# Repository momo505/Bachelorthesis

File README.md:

# Bachelorthesis
Repo für Bachelorarbeit

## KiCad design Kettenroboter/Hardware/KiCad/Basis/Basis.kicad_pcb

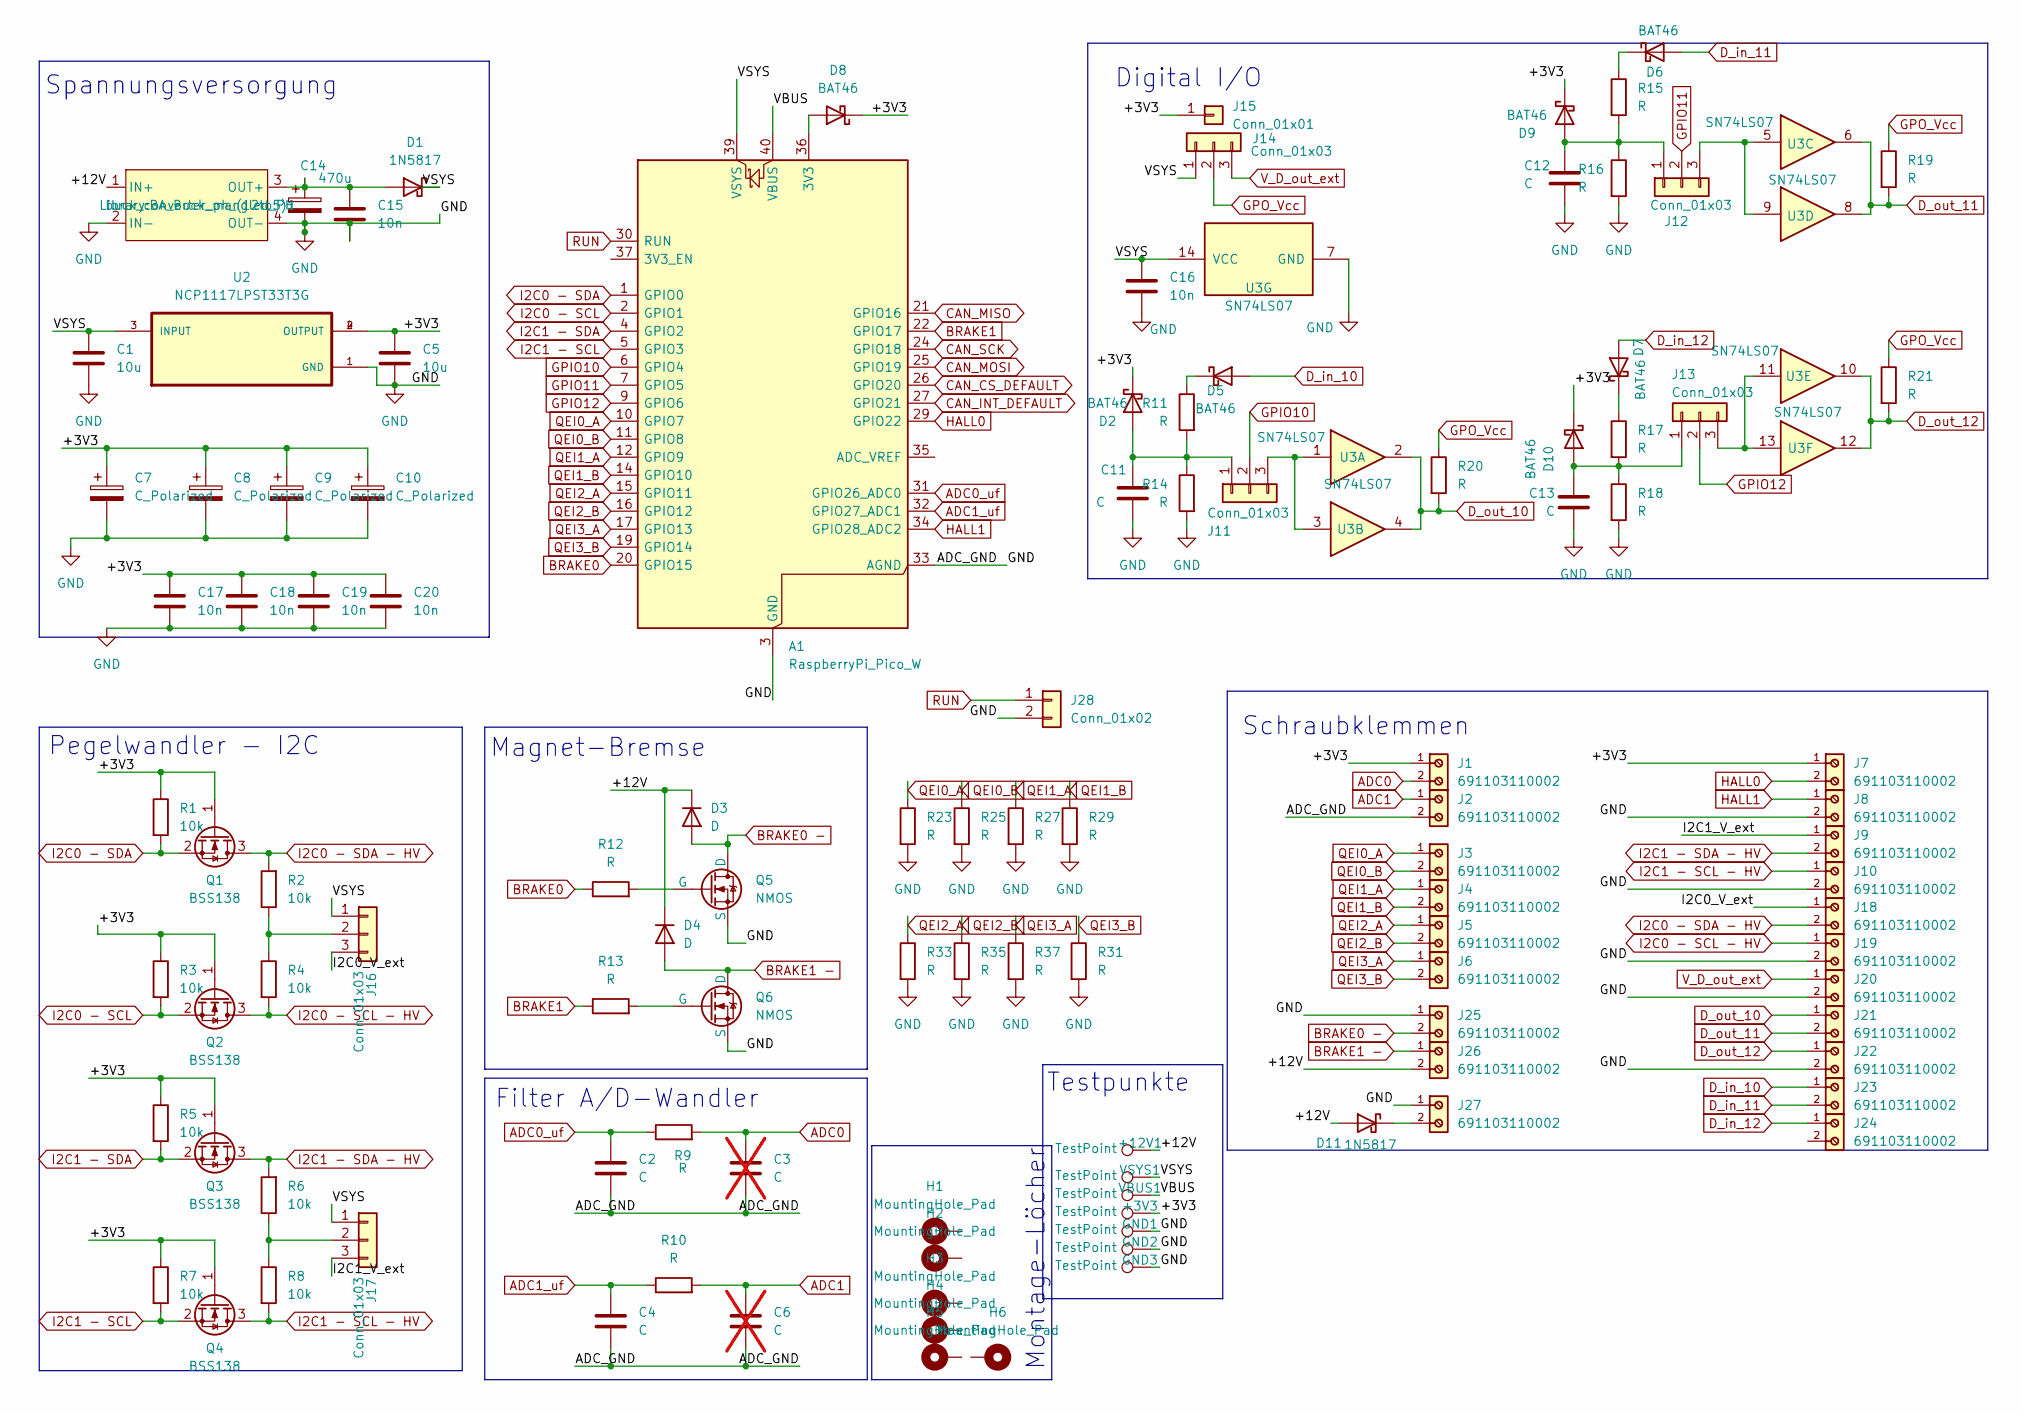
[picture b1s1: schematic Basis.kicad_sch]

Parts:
+3V3, +12V1: TestPoint; TestPoint_Pad_D2.5mm
A1: RaspberryPi_Pico_W; RaspberryPi_Pico_Common_THT
C1, C5: 10u; C_1206_3216Metric_Pad1.33x1.80mm_HandSolder
C2, C4, C11, C12, C13: C; C_1206_3216Metric_Pad1.33x1.80mm_HandSolder
C3, C6: C; C_1206_3216Metric_Pad1.33x1.80mm_HandSolder; not fitted
C7, C8, C9, C10: C_Polarized; CP_Radial_D5.0mm_P2.50mm
C14: 470u; CP_Radial_D5.0mm_P2.50mm
C15, C16, C17, C18, C19, C20: 10n; C_1206_3216Metric_Pad1.33x1.80mm_HandSolder
D1, D11: 1N5817; D_DO-41_SOD81_P10.16mm_Horizontal
D2, D5, D6, D7, D8, D9, D10: BAT46; D_DO-35_SOD27_P7.62mm_Horizontal
D3, D4: D; D_5KPW_P7.62mm_Vertical_AnodeUp
GND1, GND2, GND3: TestPoint; TestPoint_Pad_D2.5mm
H1, H2: MountingHole_Pad; MountingHole_3.2mm_M3_Pad_Via
H3, H4, H5, H6: MountingHole_Pad; MountingHole_4.3mm_M4_Pad_Via
J1, J2, J3, J4, J5, J6, J7, J8, J9, J10, J18, J19, J20, J21, J22, J23, J24, J25, J26, J27: 691103110002; WR-TBL_V3_2pin_691103110002
J11, J12, J13, J14, J16, J17: Conn_01x03; PinHeader_1x03_P2.54mm_Vertical
J15: Conn_01x01; PinHeader_1x01_P2.54mm_Vertical
J28: Conn_01x02; PinHeader_1x02_P2.54mm_Vertical
Q1, Q2, Q3, Q4: BSS138; SOT-23
Q5, Q6: NMOS; SOT-23_AO3400
R1, R2, R3, R4, R5, R6, R7, R8: 10k; R_1206_3216Metric_Pad1.30x1.75mm_HandSolder
R9, R10, R11, R12, R13, R14, R15, R16, R17, R18, R19, R20, R21, R23, R25, R27, R29, R31, R33, R35, R37: R; R_1206_3216Metric_Pad1.30x1.75mm_HandSolder
U2: NCP1117LPST33T3G; NCP1117_SOT230P700X175-4N
U3: SN74LS07; SOIC127P600X175-14N
VBUS1: TestPoint; TestPoint_Pad_D2.5mm
VSYS1: TestPoint; TestPoint_Pad_D2.5mm
buck_converter_ph_(12to5)1: BA_Buck_mangled_PH

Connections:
/+3V3: +3V3.1, C5.1, C7.1, C8.1, C9.1, C10.1, C17.1, C18.1, C19.1, C20.1, D2.1 (K), D8.1 (K), D9.1 (K), D10.1 (K), J1.1, J7.1, J15.1, Q1.1 (G), Q2.1 (G), Q3.1 (G), Q4.1 (G), R1.1, R3.1, R5.1, R7.1, U2.2 (OUTPUT), U2.4 (OUTPUT)
/+12V: +12V1.1, D3.1 (K), D4.1 (K), D11.2 (A), J26.2, buck_converter_ph_(12to5)1.1 (IN+)
/I2C0_V_ext: J16.3, J18.1
/I2C1_V_ext: J9.1, J17.3
/VBUS: A1.40 (VBUS), VBUS1.1
/VSYS: A1.39 (VSYS), C1.1, C16.1, D1.1 (K), J14.1, J16.1, J17.1, U2.3 (INPUT), U3.14 (VCC), VSYS1.1
ADC0: C3.1, J1.2, R9.2
ADC0_uf: A1.31 (GPIO26_ADC0), C2.1, R9.1
ADC1: C6.1, J2.1, R10.2
ADC1_uf: A1.32 (GPIO27_ADC1), C4.1, R10.1
BRAKE0: A1.20 (GPIO15), R12.1
BRAKE0 -: D3.2 (A), J25.2, Q5.1 (D)
BRAKE1: A1.22 (GPIO17), R13.1
BRAKE1 -: D4.2 (A), J26.1, Q6.1 (D)
CAN_CS_DEFAULT: A1.26 (GPIO20)
CAN_INT_DEFAULT: A1.27 (GPIO21)
CAN_MISO: A1.21 (GPIO16)
CAN_MOSI: A1.25 (GPIO19)
CAN_SCK: A1.24 (GPIO18)
D_in_10: D5.2 (A), J23.1
D_in_11: D6.2 (A), J23.2
D_in_12: D7.2 (A), J24.1
D_out_10: J21.1, R20.2, U3.2, U3.4
D_out_11: J21.2, R19.2, U3.6, U3.8
D_out_12: J22.1, R21.2, U3.10, U3.12
GND: A1.3 (GND), A1.8 (GND), A1.13 (GND), A1.18 (GND), A1.23 (GND), A1.28 (GND), A1.33 (AGND), A1.38 (GND), C1.2, C2.2, C3.2, C4.2, C5.2, C6.2, C7.2, C8.2, C9.2, C10.2, C11.2, C12.2, C13.2, C14.2, C15.2, C16.2, C17.2, C18.2, C19.2, C20.2, GND1.1, GND2.1, GND3.1, J2.2, J8.2, J10.2, J19.2, J20.2, J22.2, J25.1, J27.1, J28.2, Q5.3 (S), Q6.3 (S), R14.2, R16.2, R18.2, R23.2, R25.2, R27.2, R29.2, R31.2, R33.2, R35.2, R37.2, U2.1 (GND), U3.7 (GND), buck_converter_ph_(12to5)1.2 (IN-), buck_converter_ph_(12to5)1.4 (OUT-)
GPIO10: A1.6 (GPIO4), J11.2
GPIO11: A1.7 (GPIO5), J12.2
GPIO12: A1.9 (GPIO6), J13.2
GPO_Vcc: J14.2, R19.1, R20.1, R21.1
HALL0: A1.29 (GPIO22), J7.2
HALL1: A1.34 (GPIO28_ADC2), J8.1
I2C0 - SCL: A1.2 (GPIO1), Q2.2 (S), R3.2
I2C0 - SCL - HV: J19.1, Q2.3 (D), R4.2
I2C0 - SDA: A1.1 (GPIO0), Q1.2 (S), R1.2
I2C0 - SDA - HV: J18.2, Q1.3 (D), R2.2
I2C1 - SCL: A1.5 (GPIO3), Q4.2 (S), R7.2
I2C1 - SCL - HV: J10.1, Q4.3 (D), R8.2
I2C1 - SDA: A1.4 (GPIO2), Q3.2 (S), R5.2
I2C1 - SDA - HV: J9.2, Q3.3 (D), R6.2
unnamed: A1.36 (3V3), D8.2 (A)
unnamed: C14.1, C15.1, D1.2 (A), buck_converter_ph_(12to5)1.3 (OUT+)
unnamed: C11.1, D2.2 (A), J11.1, R11.2, R14.1
unnamed: D5.1 (K), R11.1
unnamed: D6.1 (K), R15.1
unnamed: D7.1 (K), R17.1
unnamed: C12.1, D9.2 (A), J12.1, R15.2, R16.1
unnamed: C13.1, D10.2 (A), J13.1, R17.2, R18.1
unnamed: D11.1 (K), J27.2
unnamed: J11.3, U3.1, U3.3
unnamed: J12.3, U3.5, U3.9
unnamed: J13.3, U3.11, U3.13
unnamed: J16.2, R2.1, R4.1
unnamed: J17.2, R6.1, R8.1
unnamed: Q5.2 (G), R12.2
unnamed: Q6.2 (G), R13.2
QEI0_A: A1.10 (GPIO7), J3.1, R23.1
QEI0_B: A1.11 (GPIO8), J3.2, R25.1
QEI1_A: A1.12 (GPIO9), J4.1, R27.1
QEI1_B: A1.14 (GPIO10), J4.2, R29.1
QEI2_A: A1.15 (GPIO11), J5.1, R33.1
QEI2_B: A1.16 (GPIO12), J5.2, R35.1
QEI3_A: A1.17 (GPIO13), J6.1, R37.1
QEI3_B: A1.19 (GPIO14), J6.2, R31.1
RUN: A1.30 (RUN), J28.1
V_D_out_ext: J14.3, J20.1

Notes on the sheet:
Spannungsversorgung
Magnet-Bremse
Pegelwandler - I2C
Testpunkte
Digital I/O
Schraubklemmen
Montage-Löcher
Filter A/D-Wandler

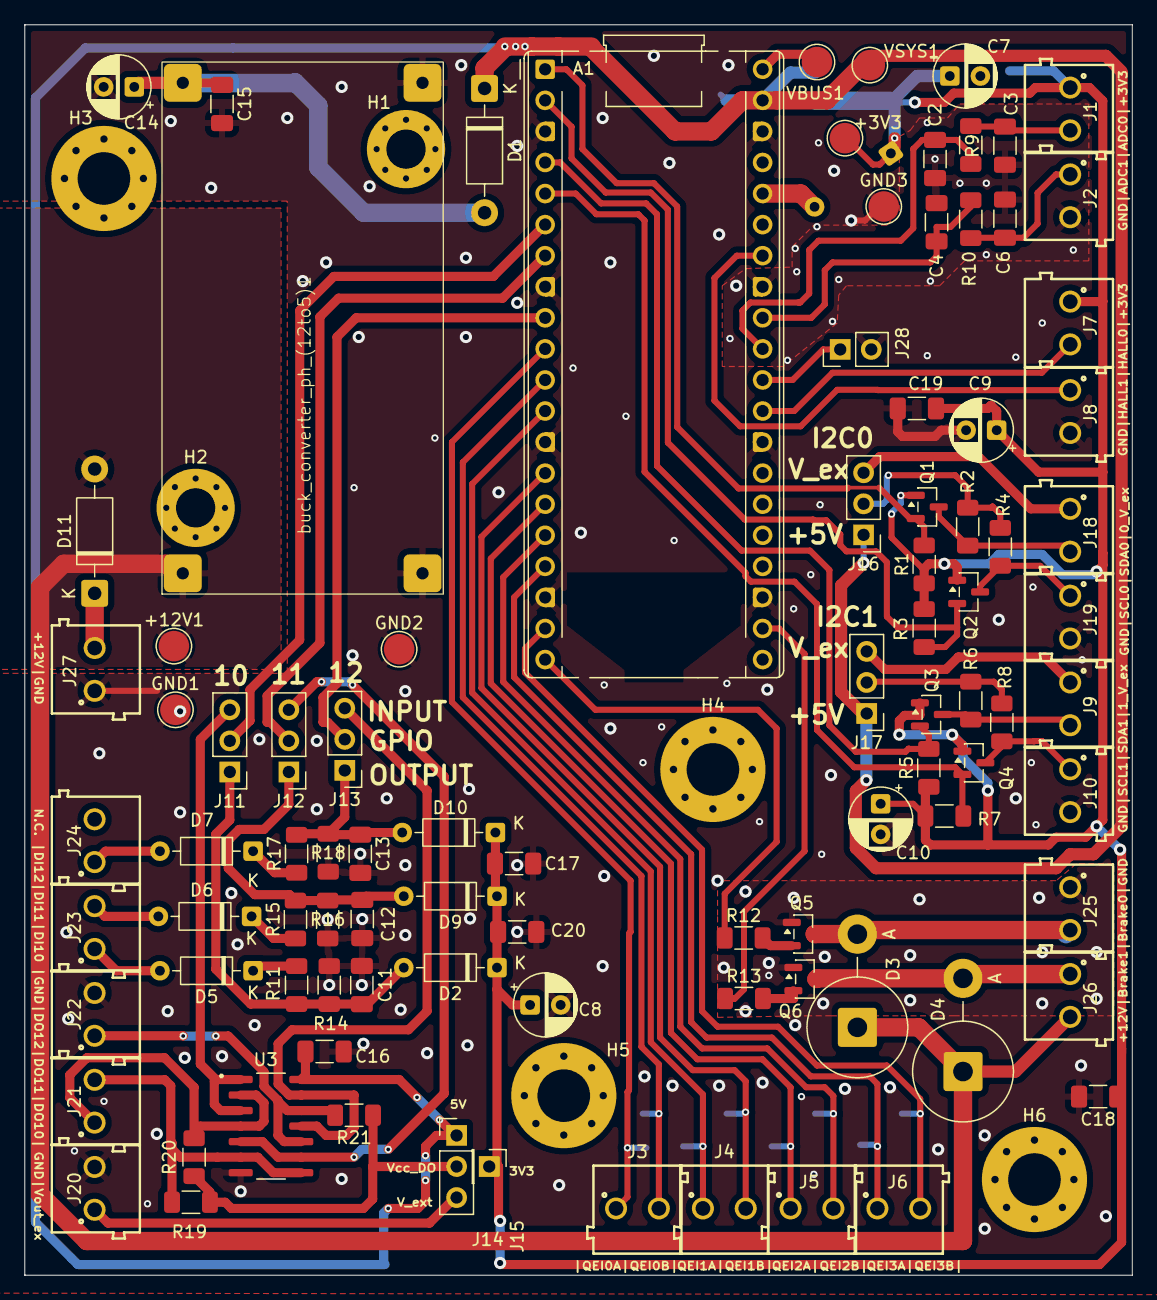
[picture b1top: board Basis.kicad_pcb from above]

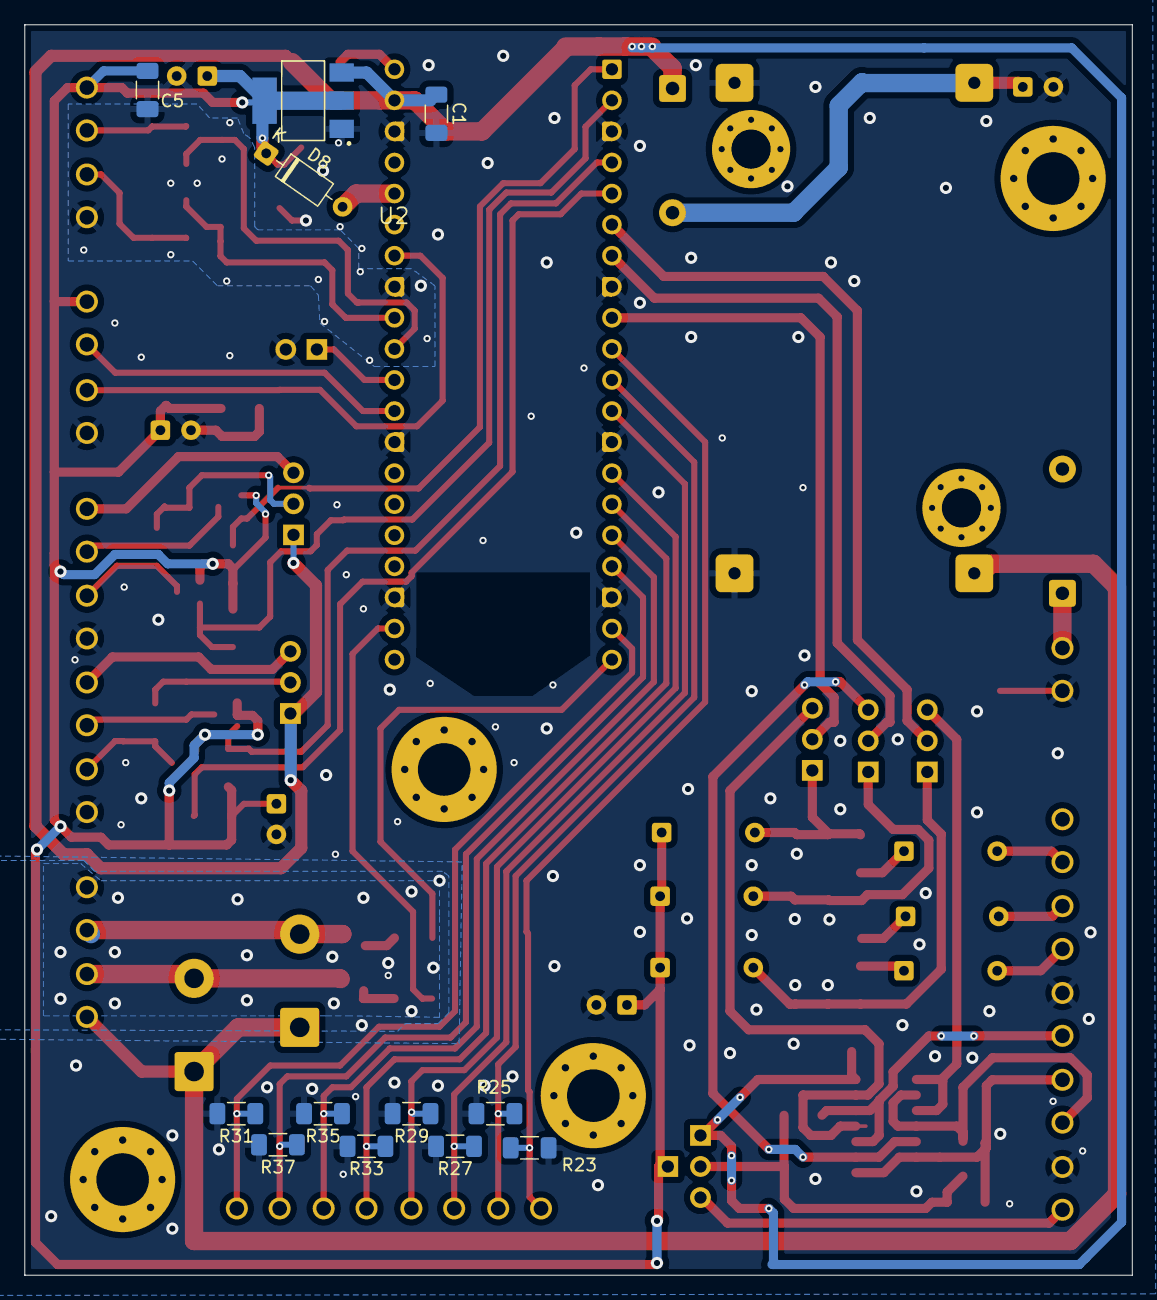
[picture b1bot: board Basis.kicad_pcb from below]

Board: 2 copper layers, 90.6 x 102.2 mm, 111 parts (12 on the bottom side), 61 nets.

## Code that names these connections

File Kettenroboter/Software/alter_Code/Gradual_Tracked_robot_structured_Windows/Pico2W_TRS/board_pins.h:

#ifndef pico2_trs_board_pinout
#define pico2_trs_board_pinout

#define I2C0_SDA 0
#define I2C0_SCL 1

#define I2C1_SDA 2
#define I2C1_SDA 3

#define DIO_1 4
#define DIO_2 5
#define DIO_3 5

#define QEI0_A 7
#define QEI0_B 8
#define QEI1_A 9
#define QEI1_B 10
#define QEI2_A 11
#define QEI2_B 12
#define QEI3_A 13
#define QEI3_B 14

#define BRAKE_A 15
#define BRAKE_B 17

#define HALL_A 29
#define HALL_B 28

#endif

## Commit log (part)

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2025-12-03 alles was bleibt vom alten Repo übernommen
2025-12-03 Add repository description to README
    Added a description for the Bachelor thesis repository.
2026-02-07 geändert: Pico2W_TRS/Pico2W_TRS.ino
2026-02-07 Zum Commit vorgemerkte Änderungen: neue Datei: KiCad/Basis/Basis-backups/Basis-2026-01-28_145330.zip neue Datei: KiCad/Basis/Basis-backups/Basis-2026-01-28_151514.zip neue Datei: KiCad/Basis/Basis-ba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
2026-02-12 Postbox Additions
    added code for postbox (in ino, has to move to cpp and h)
2026-02-17 neue Datei: Kettenroboter/Software/alter_Code/Gradual_Tracked_robot_structured_Windows/Pico2W_TRS/spi_helpers.cpp neue Datei: Kettenroboter/Software/alter_Code/Gradual_Tracked_robot_structured_Window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
2026-02-17 Auf Branch sw_job_division Zum Commit vorgemerkte Änderungen: geändert: Kettenroboter/Software/alter_Code/Gradual_Tracked_robot_structured_Windows/Pico2W_TRS/Pico2W_TRS.ino geändert: Kettenroboter/So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
2026-02-17 Auf Branch sw_pio_dev Zum Commit vorgemerkte Änderungen: geändert: qei.pio neue Datei: qei.pio.h
2026-02-19 Auf Branch sw_pio_dev Zum Commit vorgemerkte Änderungen: geändert: Kettenroboter/Software/alter_Code/Gradual_Tracked_robot_structured_Windows/Pico2W_TRS/Pico2W_TRS.ino geändert: Kettenroboter/Softwar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
2026-02-19 Ergänzungen Schaltung
2026-02-26 Nets korrigiert, etc
2026-02-26 Neues Pico W Symol & Footprint
2026-03-11 pcb layout fnished
2026-03-17 Fast finale Version
    Nach Crash gefixt
2026-03-19 final final final
2026-03-25 Auf Branch sw_pio_dev Zum Commit vorgemerkte Änderungen: umbenannt: pio_qei.cpp -> PIO/pio_qei.cpp umbenannt: pio_qei.h -> PIO/pio_qei.h umbenannt: qei.pio -> PIO/qei.pio umbenannt: qei.pio.h -> PIO/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
2026-04-02 neue Datei: Kettenroboter/Software/alter_Code/Gradual_Tracked_robot_structured_Windows/Pico2W_TRS/board_pins.h
2026-04-20 All Parts placed (BOM)
2026-04-20 Auf Branch sw_pio_dev Zum Commit vorgemerkte Änderungen: neue Datei: Kettenroboter/Software/Pico2W_TRS_Testup/LA-Bus-reads/MotorAB-I2C-reads/i2c.pvs neue Datei: Kettenroboter/Software/Pico2W_TRS_Test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
2026-04-29 Auf Branch sw_pio_dev Zum Commit vorgemerkte Änderungen: neue Datei: Kettenroboter/Software/Pico2W_TRS_Testup/PIO/pioasm.exe neue Datei: Kettenroboter/Software/Pico2W_TRS_Testup/PIO/qei.pio geändert: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
2026-05-26 On branch development Changes to be committed: new file: Kettenroboter/Software/Pico2W_TRS_Testup/PID.cpp new file: Kettenroboter/Software/Pico2W_TRS_Testup/PID.h modified: Kettenroboter/Software/Pic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
2026-05-26 Changes to be committed: modified: Kettenroboter/Software/Pico2W_TRS_Testup/Pico2W_TRS_Testup.ino Icorporated external Library for Pio-QEI
2026-05-29 On branch development Changes to be committed: modified: Kettenroboter/Software/Pico2W_TRS_Testup/PID.h new file: Kettenroboter/Software/Pico2W_TRS_Testup/PID_config.h modified: Kettenroboter/Softwar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
2026-05-29 Changes to be committed: modified: Kettenroboter/Software/Pico2W_TRS_Testup/Pico2W_TRS_Testup.ino new file: Kettenroboter/Software/Pico2W_TRS_Testup/deprPico2W_TRS_Testup_v7.txt modified: Kettenrobot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
2026-06-02 modified: Kettenroboter/Software/Pico2W_TRS_Testup/Pico2W_TRS_Testup.ino modified: Kettenroboter/Software/Pico2W_TRS_Testup/build/rp2040.rp2040.rpipico2w/Pico2W_TRS_Testup.ino.bin modified: Kettenrob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
2026-06-08 Nur kleine Anpassung an command-enums
2026-06-16 modified: Kettenroboter/Software/Pico2W_TRS_Testup/Pico2W_TRS_Testup.ino new file: Kettenroboter/Software/Pico2W_TRS_Testup/aktuellesPico2W_TRS_Testup.txt
